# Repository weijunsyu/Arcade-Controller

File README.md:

# Arcade-Controller
- Collection of CAD files for custom arcade controllers.
- Recommended total top panel thickness (including any acrylic panels) to not exceed 10mm.
- Recommended total top panel thickness is reduced to 3mm for snap-in buttons with a minimum thickness of 2mm.
- Plate mount MX-style keyboard switches require a structural panel (the plate) to be 1.5mm (+/- 0.1mm) thick to be properly mounted!
- Most .dxf files are imperial but some are metric. If in doubt, check the metadata (HEADER variable: $INSUNITS; 1:=inches, 4:=millimeter)

## Industrial Arcade Controller
*SPECIAL CONSIDERATIONS: Designed to be very modular; however, assembly requires 6 custom support blocks of which are difficult to manufacture. Support blocks are easily the most costly component in this build. These support blocks are essentially the "core" of the entire build.*
- Dimensions: 14.75" x 9.25" x (2 + top and bottom panel thickness)" Note: If side/front/back panels are significantly thick, outside dimensions may not be accurate.
- Can be easily modifed for any height, length, material, etc.
- Designed to be assembled with 6 support blocks and M4 machine screws (26 screws total).
- Most mounting holes are sized for a VERY close fit (d=4.04mm for M4); relax the tolerences if not using cnc to do manufacturing.
- Uses a standard Neutrik USB A-B connector (D-cut panel sizing).
- Panels are suffixed "Template" if they are meant to be modified with a layout before manufacture.
- "Cover" panels are optional panels that are meant to be the outermost panels (top/bottom). In the "Slot and Tab" version, these panels can be used to cover the exposed slots to give a more clean look.
1. **Accessories:**
    - NOTE: Some accessories require specific panels to be chosen!
    - D-panel Covers:
        - The 1x cover is universal and fits any d-panel cutout. (Identical to the cover found in the Parts folder.)
        - The 2-5x covers are designed for any panel with the "combined" keyword in the file name; used to cover multiple ports at once.
2. **Partial Templates:**
    - Template files that can be used to block in important features.
3. **Slot and Tab:**
    - Further organized by subfolders of which denote the thickness of the panels needed.
    - These panels have an additional slot and tab structure to further support the assembly.
4. **Supports:**
    - Support blocks can be machined from 1/2" square stock.
    - Meant to be tapped with M4 threads.
    - If machining supports by hand or if looser tolerences are desired, consider widening all panel mounting holes (M4) to d=4.5mm or even d=4.8mm to accommodate imperfect machining on support blocks.
    - STEP file and technical drawing is provided.
5. **Thickness Agnostic:**
    - Panels that do not have any protrusions to facilate the use of any thickness panel. This includes the use of combinations of various panel thicknesses in the same controller.

## Layouts
- Various layouts for button placements.
- Contains folders for different types of layouts:
    - Master Layouts: layouts with all lines for various iterations of which need to be modified prior to use.
    - Partial Layouts: layouts containing only partial cutouts, mainly for use when designing custom layouts not iterating off any master layout.
    - Finished Layouts: layouts that are finished and ready-to-cut. Contains various iterations of pre-modified master layouts and some unique layouts.
- Subfolders further segregate based on style of action button placement such as sega2P, viewlix, noir, etc.

## Mods
- Modifications of exisiting products.

## Parts
- Various arcade parts.
- Files contain a mix of imperial and metric units! (Inches/Millimeter).

## References
- Collection of reference files.

## Tools
- Collection of custom tools. 

# Technical
- MX-style keyboard switches:
    - plate thickness: 1.5mm +/- 0.1mm (0.059" +/- 0.004")
    - 30mm caps: d=1"
    - 24mm caps: d=0.85"
- D-shape housing (Neutrik NAUSB-W):
    - centre cutout: d=0.935" r=0.4675"
    - mounting holes: d=0.13" r=0.065"
- 30mm btn: d=30.25mm (1.19094488")
    - radius: 0.59547244"
- 24mm btn: d=24.2mm (0.95275590")
    - radius: 0.47637795"
    - NOTE: Crown 202 use r=0.482"
- J-lever mounting hole: d=22mm
    - radius: 0.433071"
    - NOTE: Official recommended diameter is 24mm
- K-lever mounting hole: d=35mm
    - radius: 0.6889764" (17.6mm)
- M2 d=2.39mm (0.099") r=1.195mm (0.0495")
    - Thread d=1.66mm (0.065") r=0.83mm (0.033")
- M2.5 d=2.49mm (0.103") r=1.245mm (0.0515")
- M3 d=3.18mm (0.130") r=1.59mm (0.065")
    - Close fit d=3.2mm (0.126") r=1.6mm (0.063")
    - Normal fit d=3.4mm (0.134") r=1.7mm (0.067")
    - Loose fit d=3.6mm (0.142") r=1.8mm (0.071")
- M4 d=4.04mm (0.164") r=2.02mm (0.082")
    - 0.005" fit d=4.04mm (0.164") r=2.02mm (0.082")
    - Close fit d=4.3mm (0.169") r=2.15mm (0.085")
    - Normal fit d=4.5mm (0.177") r=2.25mm (0.089")
    - 0.009" fit d=4.6mm (0.182") r=2.31mm (0.091")
    - Loose fit d=4.8mm (0.189") r=2.4mm (0.095")
- M5 d=5.00mm (0.202") r=2.50mm (0.101")
- M6 d=6.35mm (0.255") r=3.175mm (0.1275")
- M8 d=8.00mm (0.320") r=4.00mm (0.16")

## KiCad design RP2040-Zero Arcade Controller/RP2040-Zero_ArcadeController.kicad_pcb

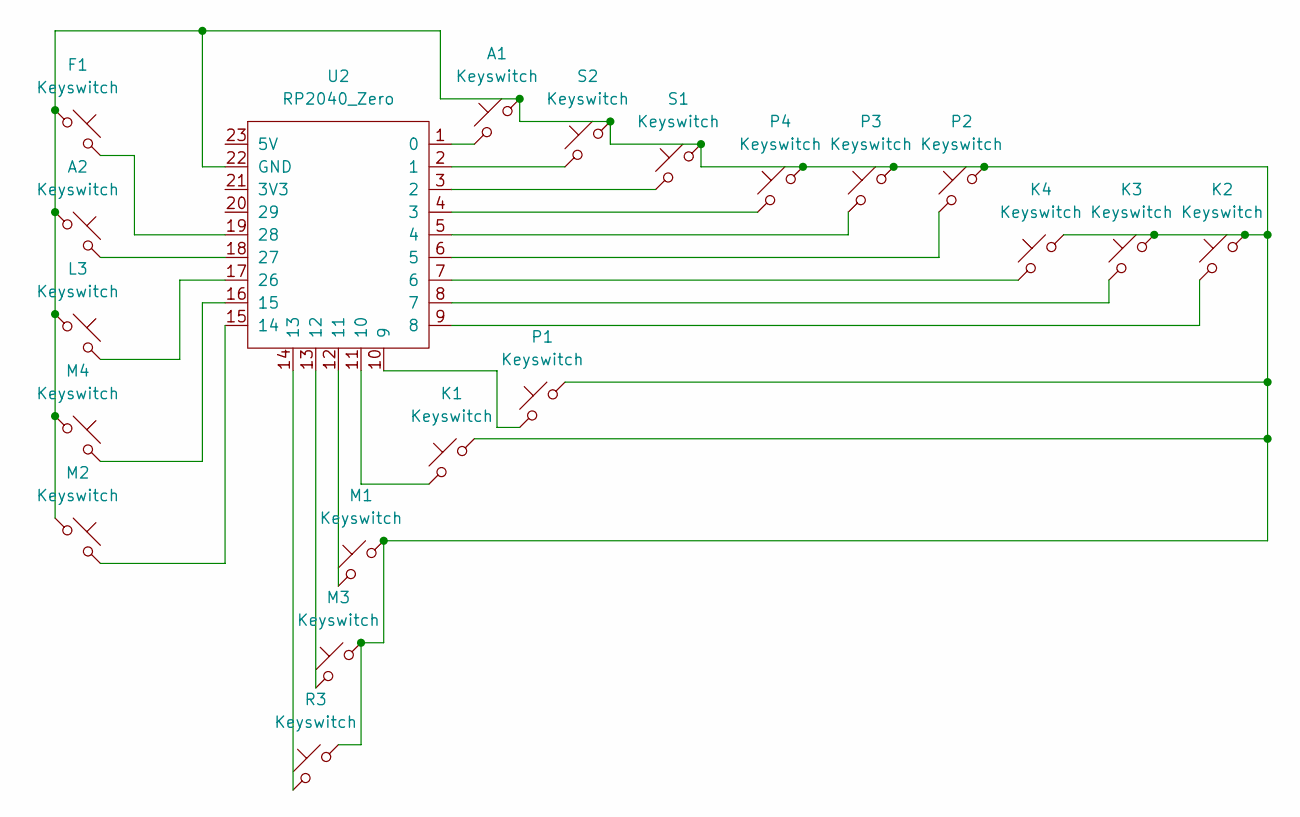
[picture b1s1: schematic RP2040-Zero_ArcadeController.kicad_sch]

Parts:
A1, A2: Keyswitch; MX_PCB_1.00u
F1: Keyswitch; MX_PCB_1.00u
K1, K2, K3, K4: Keyswitch; MX_PCB_1.00u
L3: Keyswitch; MX_PCB_1.00u
M1, M2, M3, M4: Keyswitch; MX_PCB_1.00u
P1, P2, P3, P4: Keyswitch; MX_PCB_1.00u
R3: Keyswitch; MX_PCB_1.00u
S1, S2: Keyswitch; MX_PCB_1.00u
U2: RP2040_Zero

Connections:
unnamed: A1.2, U2.1 (0)
unnamed: S2.2, U2.2 (1)
unnamed: S1.2, U2.3 (2)
unnamed: P4.2, U2.4 (3)
unnamed: P3.2, U2.5 (4)
unnamed: P2.2, U2.6 (5)
unnamed: K4.2, U2.7 (6)
unnamed: K3.2, U2.8 (7)
unnamed: K2.2, U2.9 (8)
unnamed: P1.2, U2.10 (9)
unnamed: K1.2, U2.11 (10)
unnamed: M1.2, U2.12 (11)
unnamed: M3.2, U2.13 (12)
unnamed: R3.2, U2.14 (13)
unnamed: M2.2, U2.15 (14)
unnamed: M4.2, U2.16 (15)
unnamed: L3.2, U2.17 (26)
unnamed: A2.2, U2.18 (27)
unnamed: F1.2, U2.19 (28)
unnamed: A1.1, A2.1, F1.1, K1.1, K2.1, K3.1, K4.1, L3.1, M1.1, M2.1, M3.1, M4.1, P1.1, P2.1, P3.1, P4.1, R3.1, S1.1, S2.1, U2.22 (GND)

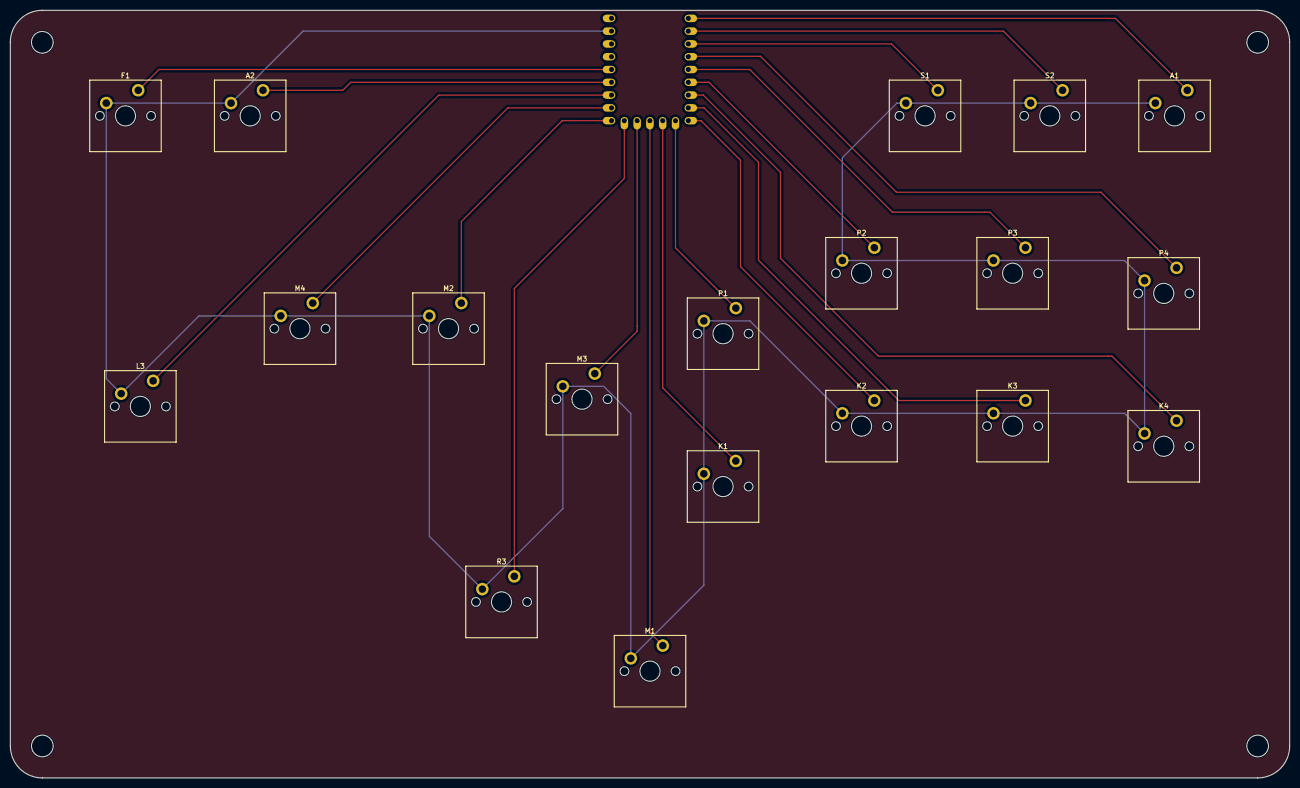
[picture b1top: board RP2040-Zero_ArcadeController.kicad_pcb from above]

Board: 2 copper layers, 254.0 x 152.4 mm, 20 parts (0 on the bottom side), 20 nets.

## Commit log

2023-09-16 Init
2023-09-16 cleanup
2023-09-16 layout cleanup
2023-09-17 new layout; shiokenstar modified
2023-09-19 layout updates
2023-09-22 Layout modification
2023-09-26 references and parts
2023-09-30 references
2023-10-15 update of the metal controller
2023-10-21 Arcade Controller
2025-06-28 Add Sanjuks V3P Square Gates
2025-06-28 Update Support
2025-07-02 Add Sanjuks V3R all-in-one shaft assembly
2026-06-14 add layout
